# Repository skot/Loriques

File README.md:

Loriques is a solar powered Meshtastic LoRa gateway. *Warning: Loriques is very much a work in progress.*

- Designed to work with a small 6V solar panel. Like the [Voltaic 6 Watt Panel](https://voltaicsystems.com/6-watt-panel/)
- [EBYTE E22-900M30S](https://www.cdebyte.com/products/E22-900M30S/3) 30dBm LoRa tranciever
  - Untested; I picked this because it's in the Meshtastic supported LoRa ISM band, and it has one of the highest listed output power of LoRa modules.
  - Selecting a good high-gain antenna for this module is TBD.
- ESP32S3 WiFi and BLE SoC
- OLED Display
- Holders for three 18650 Lithium Ion batteries
- MCP73871 Solar charge controller
  - Optimized for solar charging and load sharing, but not a "true MPPT" controller. More info from [Adafruit](https://learn.adafruit.com/usb-dc-and-solar-lipoly-charger/design-notes)
- MAX17263 Battery fuel Guage
- HDC3020 Temperature and humidity sensor
  - This is helpful for monitoring how waterproof your outdoor enclosure is. 
- Very low noise, filtered 3.3V voltage regulator
- PCB designed to fit into the [Polycase ML-46F](https://www.polycase.com/ml-46f#ML-46F*15) Outdoor NEMA Enclosure
- ESP32 Firmware is **not** started yet!
  - There are some big challenges here, like getting the ESP32S3 and it's radios in, and out of a low power state.

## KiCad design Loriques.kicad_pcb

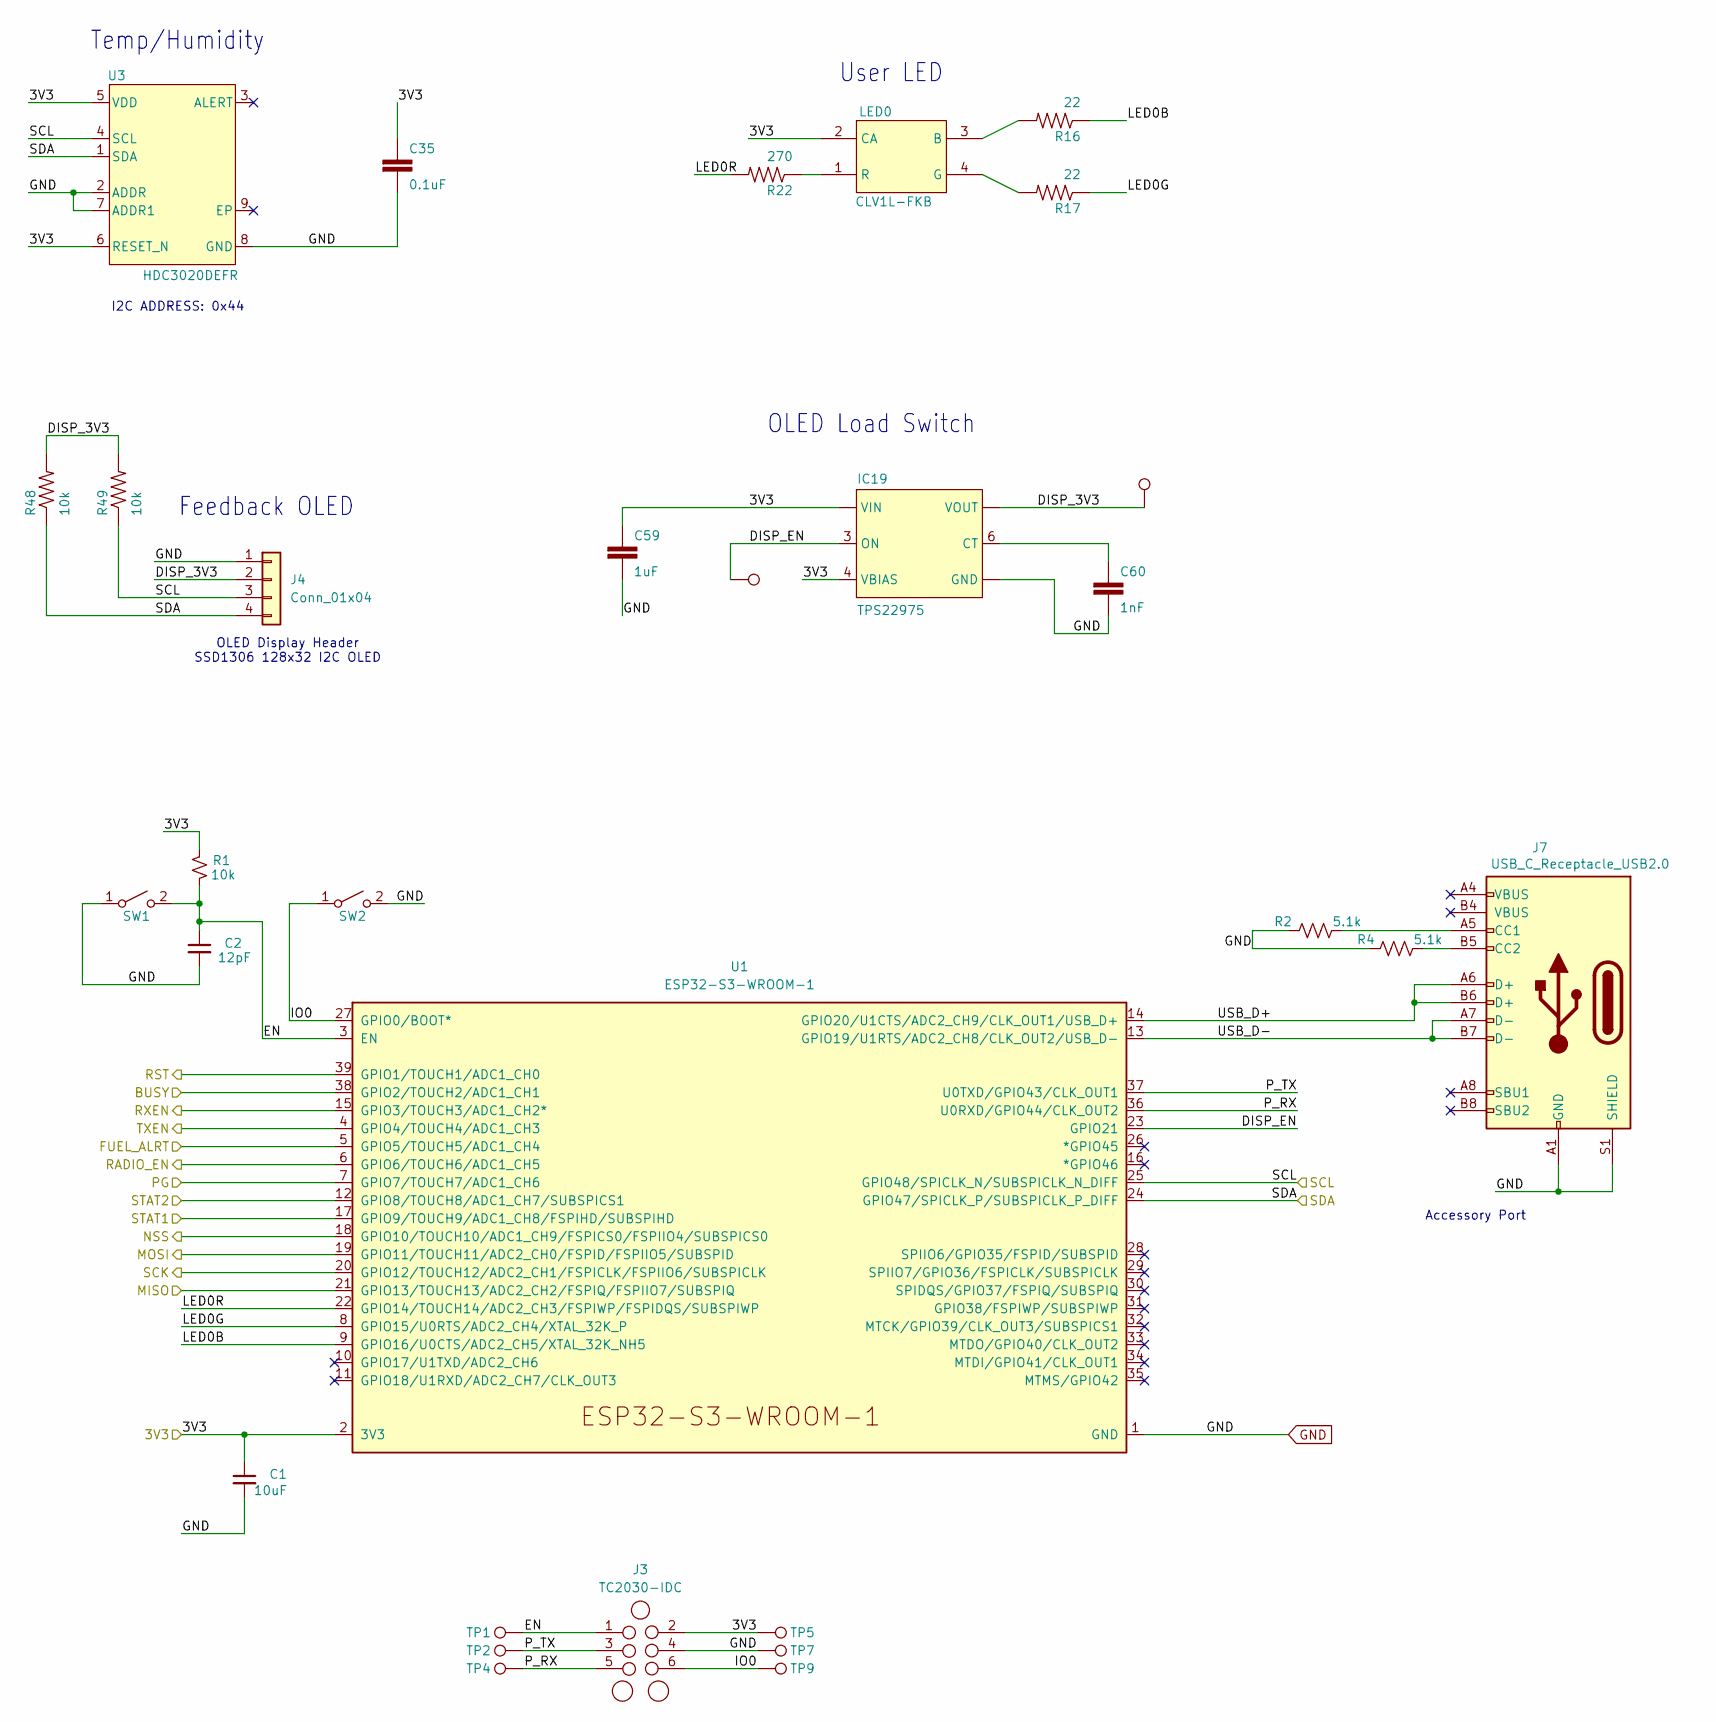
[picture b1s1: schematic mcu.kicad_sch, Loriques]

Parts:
C1: 10uF; C_0603_1608Metric; Voltage 25V; PARTNO GRM188R61E106KA73D
C2: 12pF; C_0402_1005Metric; Voltage 50V; PARTNO CC0402JRNPO9BN120
C35: 0.1uF; C_0402_1005Metric; PARTNO CL05B104KO5NNNC
C59: 1uF; C_0402_1005Metric; PARTNO GRT155R61E105KE01D
C60: 1nF; C_0402_1005Metric; PARTNO CC0402KRX7R8BB102
IC19: TPS22975; WSON8; PARTNO TPS22975DSGR
J3: TC2030-IDC; Tag-Connect_TC2030-IDC-NL_2x03_P1.27mm_Vertical
J4: Conn_01x04; PinHeader_1x04_P2.54mm_Vertical_shifted
J7: USB_C_Receptacle_USB2.0; CONN_12402032E202A_AMP; PARTNO 12402032E202A
LED0: CLV1L-FKB; PLCC140P350X320X210-4; PARTNO CLV1A-FKB-CK1VW1DE1BB7C3C3
R1: 10k; R_0402_1005Metric; PARTNO RC0402JR-0710KL
R2, R4: 5.1k; R_0402_1005Metric; PARTNO RMCF0402JT5K10; LCSC C25905
R16, R17: 22; R_0402_1005Metric; PARTNO CRGCQ0402J22R
R22: 270; R_0402_1005Metric; PARTNO CRGCQ0402F270R
R48, R49: 10k; R_0402_1005Metric
SW1: SWITCH-SPST; SW_CS1213AGF260_CRS; PARTNO CS1213AGF260; LCSC C5578986
SW2: SWITCH-SPST; SW_CS1213AGF260_CRS; PARTNO CS1213AGF260
S_3V1: TEST-POINT3X5; TestPoint_Pad_D1.5mm
TP1, TP2, TP4, TP5, TP7, TP9: TestPoint; TestPoint_Pad_D1.5mm
TP3: TEST-POINT3X5; TestPoint_Pad_D1.5mm
U1: ESP32-S3-WROOM-1; PARTNO ESP32-S3-WROOM-1-N16R8
U3: HDC3020DEFR; DEF0008A-IPC_A; PARTNO HDC3020DEFR

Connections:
/FUEL: U1.5 (GPIO5/TOUCH5/ADC1_CH4); also elsewhere on the board
/MCU/3V3: C1.1, C35.1, C59.1, IC19.1 (VIN), IC19.2 (VIN), IC19.4 (VBIAS), J3.2, LED0.2 (CA), R1.2, TP5.1, U1.2 (3V3), U3.5 (VDD), U3.6 (RESET_N); also elsewhere on the board
/MCU/DISP_3V3: IC19.7 (VOUT), IC19.8 (VOUT), J4.2, R48.2, R49.2, S_3V1.1
/MCU/DISP_EN: IC19.3 (ON), TP3.1, U1.23 (GPIO21)
/MCU/EN: C2.1, J3.1, R1.1, SW1.2 (B), TP1.1, U1.3 (EN)
/MCU/IO0: J3.6, SW2.1 (A), TP9.1, U1.27 (GPIO0/BOOT*)
/MCU/LED0B: R16.1, U1.9 (GPIO16/U0CTS/ADC2_CH5/XTAL_32K_NH5)
/MCU/LED0G: R17.1, U1.8 (GPIO15/U0RTS/ADC2_CH4/XTAL_32K_P)
/MCU/LED0R: R22.2, U1.22 (GPIO14/TOUCH14/ADC2_CH3/FSPIWP/FSPIDQS/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)
/MCU/PG: U1.7 (GPIO7/TOUCH7/ADC1_CH6); also elsewhere on the board
/MCU/P_RX: J3.5, TP4.1, U1.36 (U0RXD/GPIO44/CLK_OUT2)
/MCU/P_TX: J3.3, TP2.1, U1.37 (U0TXD/GPIO43/CLK_OUT1)
/MCU/RADIO_EN: U1.6 (GPIO6/TOUCH6/ADC1_CH5); also elsewhere on the board
/MCU/STAT1: U1.17 (GPIO9/TOUCH9/ADC1_CH8/FSPIHD/SUBSPIHD); also elsewhere on the board
/MCU/STAT2: U1.12 (GPIO8/TOUCH8/ADC1_CH7/SUBSPICS1); also elsewhere on the board
/MCU/USB_D+: J7.A6 (D+), J7.B6 (D+), U1.14 (GPIO20/U1CTS/ADC2_CH9/CLK_OUT1/USB_D+)
/MCU/USB_D-: J7.A7 (D-), J7.B7 (D-), U1.13 (GPIO19/U1RTS/ADC2_CH8/CLK_OUT2/USB_D-)
/Radio/BUSY_MCU: U1.38 (GPIO2/TOUCH2/ADC1_CH1); also elsewhere on the board
/Radio/MISO_MCU: U1.21 (GPIO13/TOUCH13/ADC2_CH2/FSPIQ/FSPIIO7/S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); also elsewhere on the board
/Radio/MOSI_MCU: U1.19 (GPIO11/TOUCH11/ADC2_CH0/FSPID/FSPIIO5/S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); also elsewhere on the board
/Radio/NSS_MCU: U1.18 (GPIO10/TOUCH10/ADC1_CH9/FSPICS0/FSPIIO4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); also elsewhere on the board
/Radio/RST_MCU: U1.39 (GPIO1/TOUCH1/ADC1_CH0); also elsewhere on the board
/Radio/RXEN_MCU: U1.15 (GPIO3/TOUCH3/ADC1_CH2*); also elsewhere on the board
/Radio/SCK_MCU: U1.20 (GPIO12/TOUCH12/ADC2_CH1/FSPICLK/FSPIIO6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); also elsewhere on the board
/Radio/TXEN_MCU: U1.4 (GPIO4/TOUCH4/ADC1_CH3); also elsewhere on the board
/SCL: J4.3, R49.1, U1.25 (GPIO48/SPICLK_N/SUBSPICLK_N_DIFF), U3.4 (SCL); also elsewhere on the board
/SDA: J4.4, R48.1, U1.24 (GPIO47/SPICLK_P/SUBSPICLK_P_DIFF), U3.1 (SDA); also elsewhere on the board
GND: C1.2, C2.2, C35.2, C59.2, C60.2, IC19.5 (GND), IC19.PP (GND), J3.4, J4.1, J7.A1 (GND), J7.B1 (GND), J7.S1 (SHIELD), R2.1, R4.1, SW1.1 (A), SW2.2 (B), TP7.1, U1.1 (GND), U1.40 (GND), U1.41 (GND), U3.2 (ADDR), U3.7 (ADDR1), U3.8 (GND); also elsewhere on the board
unnamed: C60.1, IC19.6 (CT)
unnamed: J7.A5 (CC1), R2.2
unnamed: J7.B5 (CC2), R4.2
unnamed: LED0.3 (B), R16.2
unnamed: LED0.4 (G), R17.2
unnamed: LED0.1 (R), R22.1

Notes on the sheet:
Temp/Humidity
Accessory Port
Feedback OLED
OLED Load Switch
OLED Display Header SSD1306 128x32 I2C OLED
User LED
I2C ADDRESS: 0x44

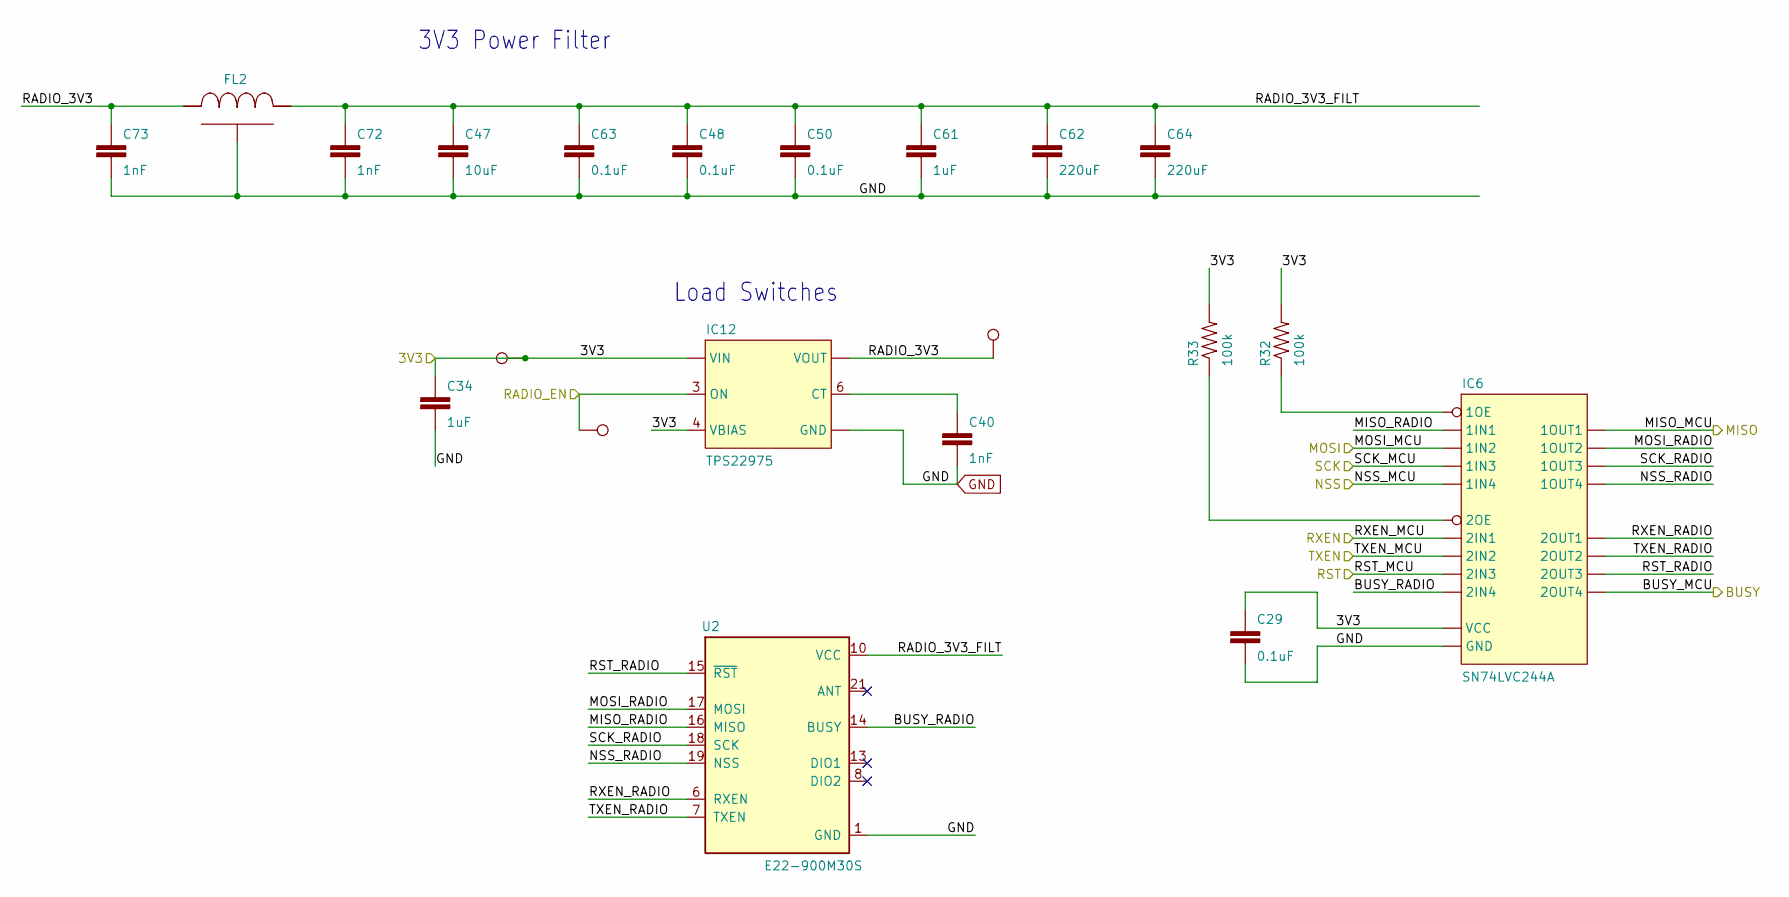
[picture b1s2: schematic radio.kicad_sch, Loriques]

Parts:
C29, C48, C50, C63: 0.1uF; C_0402_1005Metric; PARTNO CL05A104KA5NNNC
C34, C61: 1uF; C_0402_1005Metric; PARTNO GRT155R61E105KE01D
C40, C72, C73: 1nF; C_0402_1005Metric; PARTNO CC0402KRX7R8BB102
C47: 10uF; C_1206_3216Metric; PARTNO CL31B106KOHNNWE
C62, C64: 220uF; C_1210_3225Metric; PARTNO GRM32ER60J227ME05L
FL2: YFF31HC2A104MT000N; PARTNO YFF31HC2A105MT000N
IC6: SN74LVC244A; R-PVQFN-N20
IC12: TPS22975; WSON8; PARTNO TPS22975DSGR
R32, R33: 100k; R_0402_1005Metric; PARTNO RC0402FR-07100KL
S_3V3: TEST-POINT3X5; TestPoint_Pad_D1.5mm
TP6, TP8: TEST-POINT3X5; TestPoint_Pad_D1.5mm
U2: E22-900M30S

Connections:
/MCU/3V3: C29.1, C34.1, IC6.20 (VCC), IC12.1 (VIN), IC12.2 (VIN), IC12.4 (VBIAS), R32.2, R33.2, TP6.1; also elsewhere on the board
/MCU/RADIO_EN: IC12.3 (ON), TP8.1; also elsewhere on the board
/Radio/BUSY_MCU: IC6.3 (2OUT4); also elsewhere on the board
/Radio/BUSY_RADIO: IC6.17 (2IN4), U2.14 (BUSY)
/Radio/MISO_MCU: IC6.18 (1OUT1); also elsewhere on the board
/Radio/MISO_RADIO: IC6.2 (1IN1), U2.16 (MISO)
/Radio/MOSI_MCU: IC6.4 (1IN2); also elsewhere on the board
/Radio/MOSI_RADIO: IC6.16 (1OUT2), U2.17 (MOSI)
/Radio/NSS_MCU: IC6.8 (1IN4); also elsewhere on the board
/Radio/NSS_RADIO: IC6.12 (1OUT4), U2.19 (NSS)
/Radio/RADIO_3V3: C73.1, FL2.1, IC12.7 (VOUT), IC12.8 (VOUT), S_3V3.1
/Radio/RST_MCU: IC6.15 (2IN3); also elsewhere on the board
/Radio/RST_RADIO: IC6.5 (2OUT3), U2.15 (~RST)
/Radio/RXEN_MCU: IC6.11 (2IN1); also elsewhere on the board
/Radio/RXEN_RADIO: IC6.9 (2OUT1), U2.6 (RXEN)
/Radio/SCK_MCU: IC6.6 (1IN3); also elsewhere on the board
/Radio/SCK_RADIO: IC6.14 (1OUT3), U2.18 (SCK)
/Radio/TXEN_MCU: IC6.13 (2IN2); also elsewhere on the board
/Radio/TXEN_RADIO: IC6.7 (2OUT2), U2.7 (TXEN)
GND: C29.2, C34.2, C40.2, C47.2, C48.2, C50.2, C61.2, C62.2, C63.2, C64.2, C72.2, C73.2, FL2.GND, IC6.10 (GND), IC6.21 (GND), IC12.5 (GND), IC12.PP (GND), U2.1 (GND), U2.2 (GND), U2.3 (GND), U2.4 (GND), U2.5 (GND), U2.11 (GND), U2.12 (GND), U2.20 (GND), U2.22 (GND); also elsewhere on the board
unnamed: IC6.1 (1OE), R32.1
unnamed: IC6.19 (2OE), R33.1
unnamed: C40.1, IC12.6 (CT)
VCC: C47.1, C48.1, C50.1, C61.1, C62.1, C63.1, C64.1, C72.1, FL2.3 (2), U2.9 (VCC), U2.10 (VCC)

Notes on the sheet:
3V3 Power Filter
Load Switches

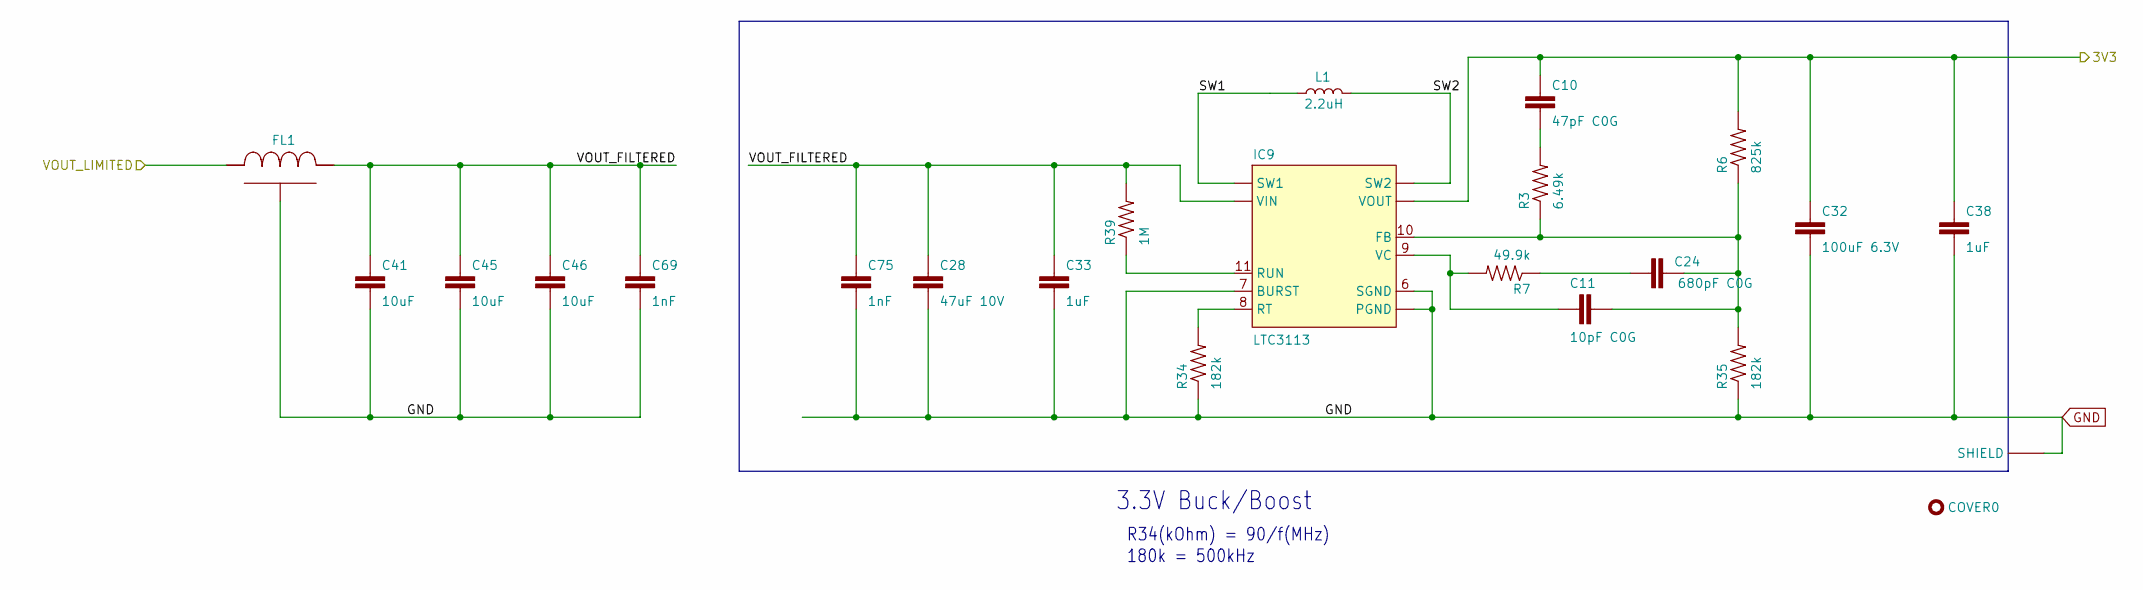
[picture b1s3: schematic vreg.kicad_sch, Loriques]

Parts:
C10: 47pF C0G; C_0402_1005Metric; PARTNO C1005C0G1H470J050BA
C11: 10pF C0G; C_0402_1005Metric; PARTNO CL05C100DB5NNNC
C24: 680pF C0G; C_0402_1005Metric; PARTNO CL05C681JB5NNNC
C28: 47uF 10V; C_1812_4532Metric; PARTNO C4532X5R1A476M280KA
C32: 100uF 6.3V; C_1812_4532Metric; PARTNO C4532X5R0J107M280KA
C33, C38: 1uF; C_0603_1608Metric; PARTNO CL10A105KA8NNNC
C41, C45, C46: 10uF; C_1206_3216Metric; PARTNO CL31B106KOHNNWE
C69, C75: 1nF; C_0402_1005Metric; PARTNO CC0402KRX7R8BB102
COVER0: BULLET; NOTHING; PARTNO MS288-10C
FL1: YFF31HC2A104MT000N; PARTNO YFF31HC2A105MT000N
IC9: LTC3113; SON50P400X500X80-17T244X434N; PARTNO LTC3113IDHD#TRPBF
L1: 2.2uH; IND_IHLP-2525CZ_VIS; PARTNO IHLP2525CZER2R2MA1
R3: 6.49k; R_0402_1005Metric; PARTNO RMCF0402FT6K49
R6: 825k; R_0402_1005Metric; PARTNO RC0402FR-07825KL
R7: 49.9k; R_0402_1005Metric; PARTNO RC0402FR-0749K9L
R34: 182k; R_0402_1005Metric; PARTNO ERJ-2RKF1823X
R35: 182k; R_0402_1005Metric; PARTNO RMCF0402FT182K
R39: 1M; R_0402_1005Metric; PARTNO CRCW04021M00FKEDC
S1: MS288-10F

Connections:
/MCU/3V3: C10.1, C32.1, C38.1, IC9.1 (VOUT), IC9.2 (VOUT), R6.2; also elsewhere on the board
/Power Input/VOUT_LIMITED: FL1.1; also elsewhere on the board
/Voltage Regulator/SW1: IC9.12 (SW1), IC9.13 (SW1), IC9.14 (SW1), L1.1
/Voltage Regulator/SW2: IC9.15 (SW2), IC9.16 (SW2), L1.2
/Voltage Regulator/VOUT_FILTERED: C28.1, C33.1, C41.1, C45.1, C46.1, C69.1, C75.1, FL1.3 (2), IC9.3 (VIN), IC9.4 (VIN), IC9.5 (VIN), R39.2
GND: C28.2, C32.2, C33.2, C38.2, C41.2, C45.2, C46.2, C69.2, C75.2, FL1.GND, IC9.6 (SGND), IC9.7 (BURST), IC9.17 (PGND), R34.1, R35.1, S1.1 (SHIELD); also elsewhere on the board
unnamed: C10.2, R3.2
unnamed: C24.1, R7.1
unnamed: C11.2, C24.2, IC9.10 (FB), R3.1, R6.1, R35.2
unnamed: IC9.8 (RT), R34.2
unnamed: IC9.11 (RUN), R39.1
unnamed: C11.1, IC9.9 (VC), R7.2

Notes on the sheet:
180k = 500kHz
R34(kOhm) = 90/f(MHz)
3.3V Buck/Boost

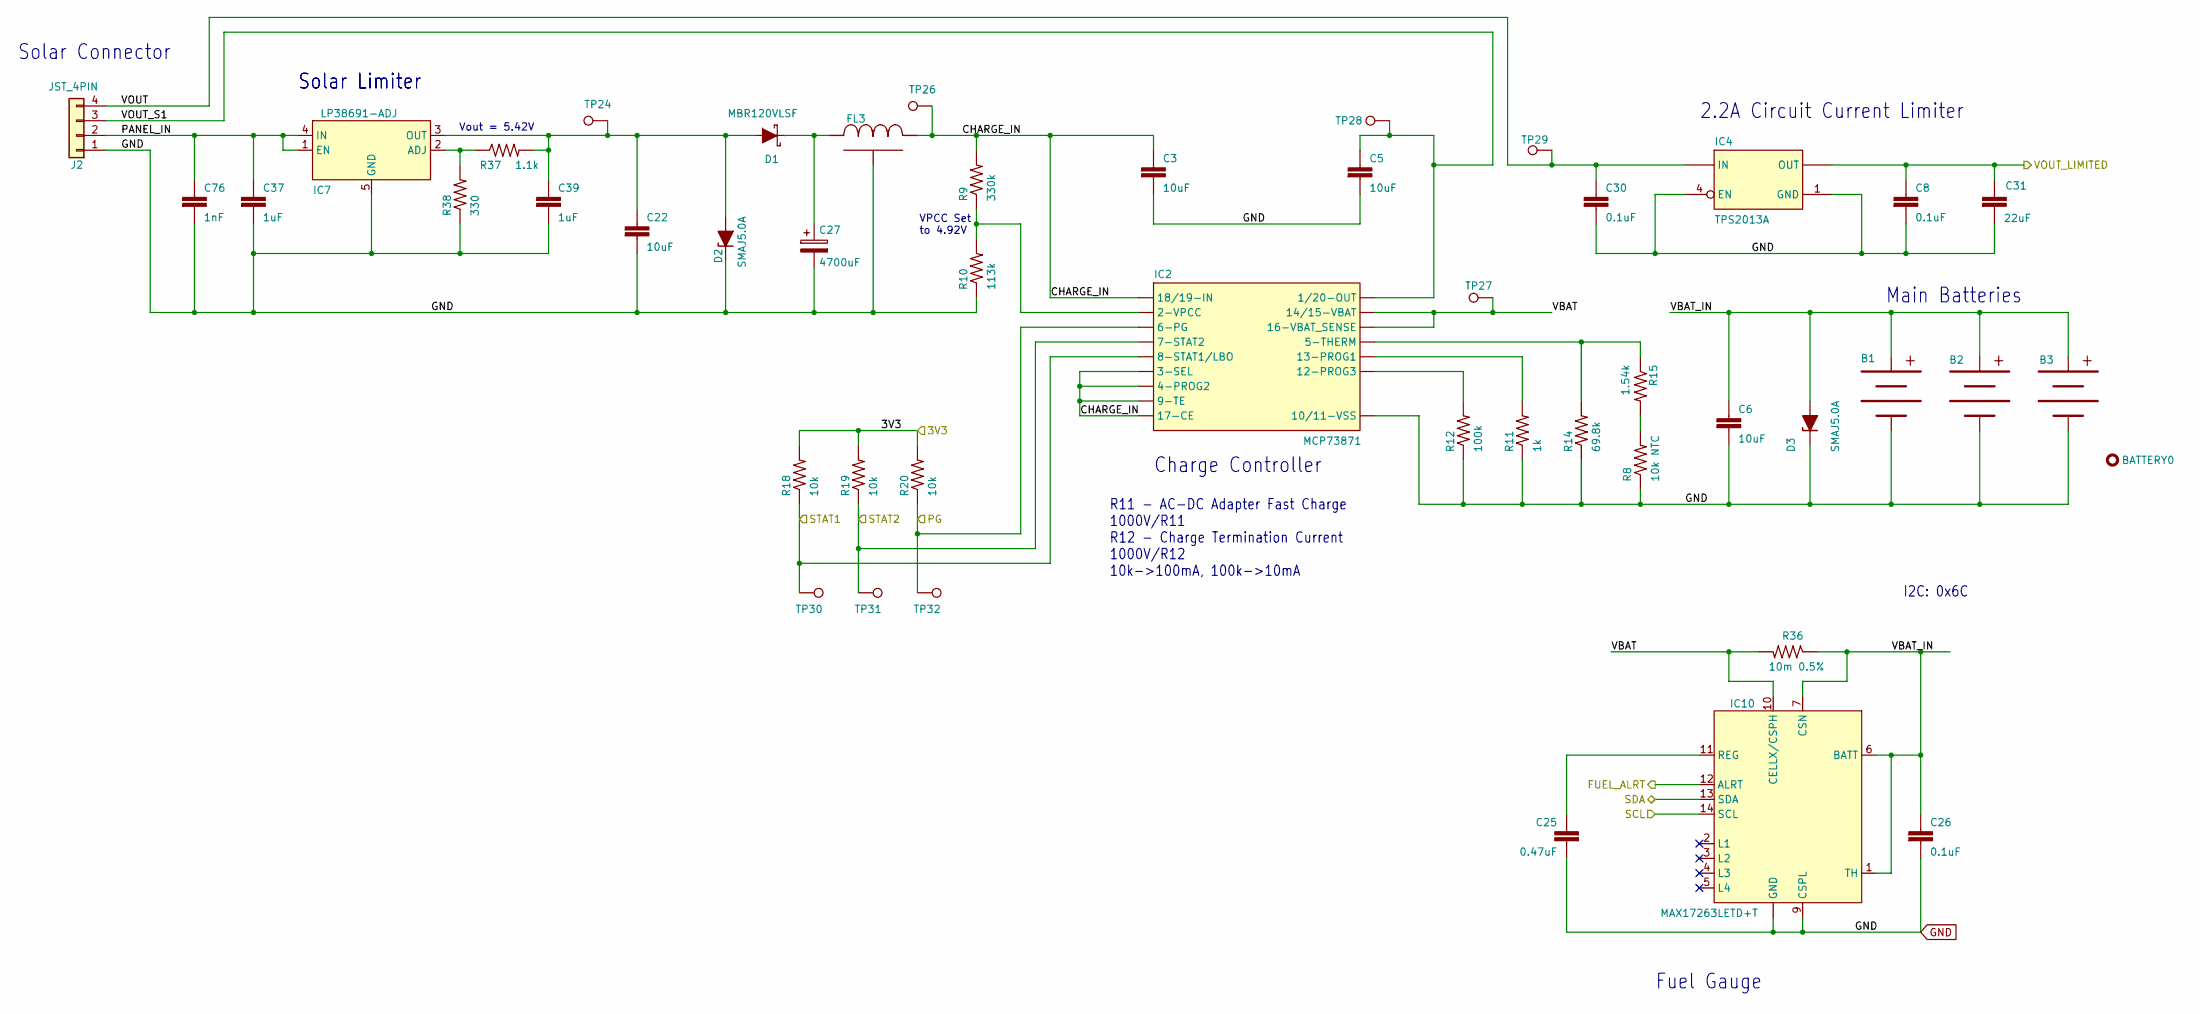
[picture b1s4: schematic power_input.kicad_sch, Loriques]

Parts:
B1, B2, B3: 18650_1042; 1042
BATTERY0: BULLET; NOTHING
C3, C5, C6, C22: 10uF; C_0603_1608Metric; PARTNO GRM188R6YA106MA73D
C8, C26, C30: 0.1uF; C_0402_1005Metric; PARTNO CL05A104KA5NNNC
C25: 0.47uF; C_0402_1005Metric; PARTNO GRT155R61E474ME01D
C27: 4700uF; CP_Radial_D16.0mm_P7.50mm; PARTNO 25PK4700MEFC16X25
C31: 22uF; C_0805_2012Metric; PARTNO GRM21BR61E226ME44L
C37, C39: 1uF; C_0402_1005Metric; PARTNO C1005X5R1V105K050BE
C76: 1nF; C_0402_1005Metric; PARTNO CC0402KRX7R8BB102
D1: MBR120VLSF; SOD−123FL; PARTNO MBR120VLSFT1G
D2, D3: SMAJ5.0A; D_SMA; PARTNO SMAJ5.0A
FL3: YFF31HC2A104MT000N; PARTNO YFF31HC2A105MT000N
IC2: MCP73871; QFN20-ML_4X4MM; PARTNO MCP73871-2CCI/ML
IC4: TPS2013A; R-PDSO-G8_NOPAD; PARTNO TPS2013AD
IC7: LP38691-ADJ; SOT-223-5; PARTNO LP38693MP-ADJ/NOPB
IC10: MAX17263LETD+T; SON40P300X300X80-15T170X230N; PARTNO MAX17263LETD+T
J2: JST_4PIN; JST-PH-4-SMT; PARTNO B4B-PH-SM4-TB
R8: 10k NTC; R_0402_1005Metric; PARTNO ERT-J0EM103J
R9: 330k; R_0402_1005Metric; PARTNO RC0402JR-07330KL
R10: 113k; R_0402_1005Metric; PARTNO RC0402FR-07113KL
R11: 1k; R_0402_1005Metric; PARTNO RC0402FR-071KL
R12: 100k; R_0402_1005Metric; PARTNO RC0402FR-07100KL
R14: 69.8k; R_0402_1005Metric; PARTNO RC0402FR-0769K8L
R15: 1.54k; R_0402_1005Metric; PARTNO RC0402FR-071K54L
R18, R19, R20: 10k; R_0402_1005Metric; PARTNO RC0402FR-0710KL
R36: 10m 0.5%; R_1206_3216Metric; PARTNO PCS1206DR0100ET
R37: 1.1k; R_0402_1005Metric; PARTNO RC0402FR-071K1L
R38: 330; R_0402_1005Metric; PARTNO RC0402FR-07330RL
TP24, TP26, TP27, TP28, TP29, TP30, TP31, TP32: TEST-POINT3X5; TestPoint_Pad_D1.5mm

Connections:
/FUEL: IC10.12 (ALRT); also elsewhere on the board
/MCU/3V3: R18.2, R19.2, R20.2; also elsewhere on the board
/MCU/PG: IC2.6 (6-PG), R20.1, TP32.1; also elsewhere on the board
/MCU/STAT1: IC2.8 (8-STAT1/LBO), R18.1, TP30.1; also elsewhere on the board
/MCU/STAT2: IC2.7 (7-STAT2), R19.1, TP31.1; also elsewhere on the board
/Power Input/CHARGE_IN: C3.1, FL3.3 (2), IC2.3 (3-SEL), IC2.4 (4-PROG2), IC2.9 (9-TE), IC2.17 (17-CE), IC2.18 (18/19-IN), IC2.19 (18/19-IN), R9.2, TP26.1
/Power Input/PANEL_IN: C37.1, C76.1, IC7.1 (EN), IC7.4 (IN), J2.2
/Power Input/VBAT: IC2.14 (14/15-VBAT), IC2.15 (14/15-VBAT), IC2.16 (16-VBAT_SENSE), IC10.10 (CELLX/CSPH), R36.2, TP27.1
/Power Input/VBAT_IN: B1.+, B2.+, B3.+, C6.1, C26.1, D3.2 (A), IC10.1 (TH), IC10.6 (BATT), IC10.7 (CSN), R36.1
/Power Input/VOUT: C30.1, IC4.2 (IN), IC4.3 (IN), J2.4, TP29.1
/Power Input/VOUT_LIMITED: C8.1, C31.1, IC4.5 (OUT), IC4.6 (OUT), IC4.7 (OUT), IC4.8 (OUT); also elsewhere on the board
/Power Input/VOUT_S1: C5.1, IC2.1 (1/20-OUT), IC2.20 (1/20-OUT), J2.3, TP28.1
/SCL: IC10.14 (SCL); also elsewhere on the board
/SDA: IC10.13 (SDA); also elsewhere on the board
GND: B1.-, B2.-, B3.-, C3.2, C5.2, C6.2, C8.2, C22.2, C25.2, C26.2, C27.2, C30.2, C31.2, C37.2, C39.2, C76.2, D2.1 (K), D3.1 (K), FL3.GND, IC2.10 (10/11-VSS), IC2.11 (10/11-VSS), IC2.EP (10/11-VSS), IC4.1 (GND), IC4.4 (EN), IC7.5 (GND), IC10.8 (GND), IC10.9 (CSPL), IC10.15 (GND), J2.1, R8.1, R10.1, R11.1, R12.1, R14.1, R38.1; also elsewhere on the board
unnamed: C27.1, D1.K, FL3.1
unnamed: C22.1, C39.1, D1.A, D2.2 (A), IC7.3 (OUT), R37.2, TP24.1
unnamed: IC2.2 (2-VPCC), R9.1, R10.2
unnamed: IC2.5 (5-THERM), R14.2, R15.1
unnamed: IC2.12 (12-PROG3), R12.2
unnamed: IC2.13 (13-PROG1), R11.2
unnamed: IC7.2 (ADJ), R37.1, R38.2
unnamed: C25.1, IC10.11 (REG)
unnamed: R8.2, R15.2

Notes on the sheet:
Vout = 5.42V
Solar Connector
Fuel Gauge
2.2A Circuit Current Limiter
R11 - AC-DC Adapter Fast Charge 1000V/R11 R12 - Charge Termination Current 1000V/R12 10k->100mA, 100k->10mA
I2C: 0x6C
Solar Limiter
Charge Controller
VPCC Set to 4.92V
Main Batteries

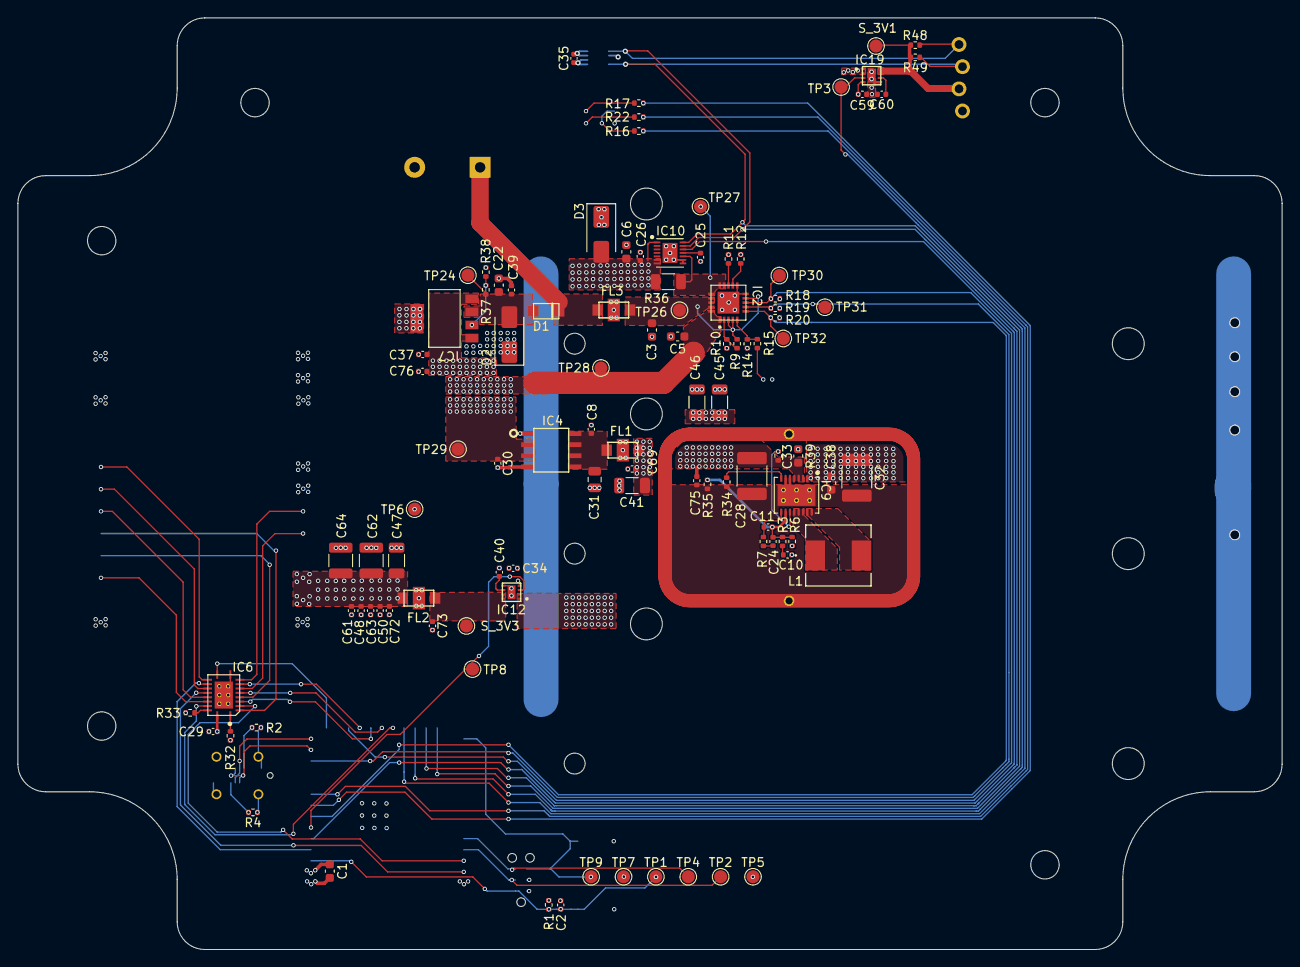
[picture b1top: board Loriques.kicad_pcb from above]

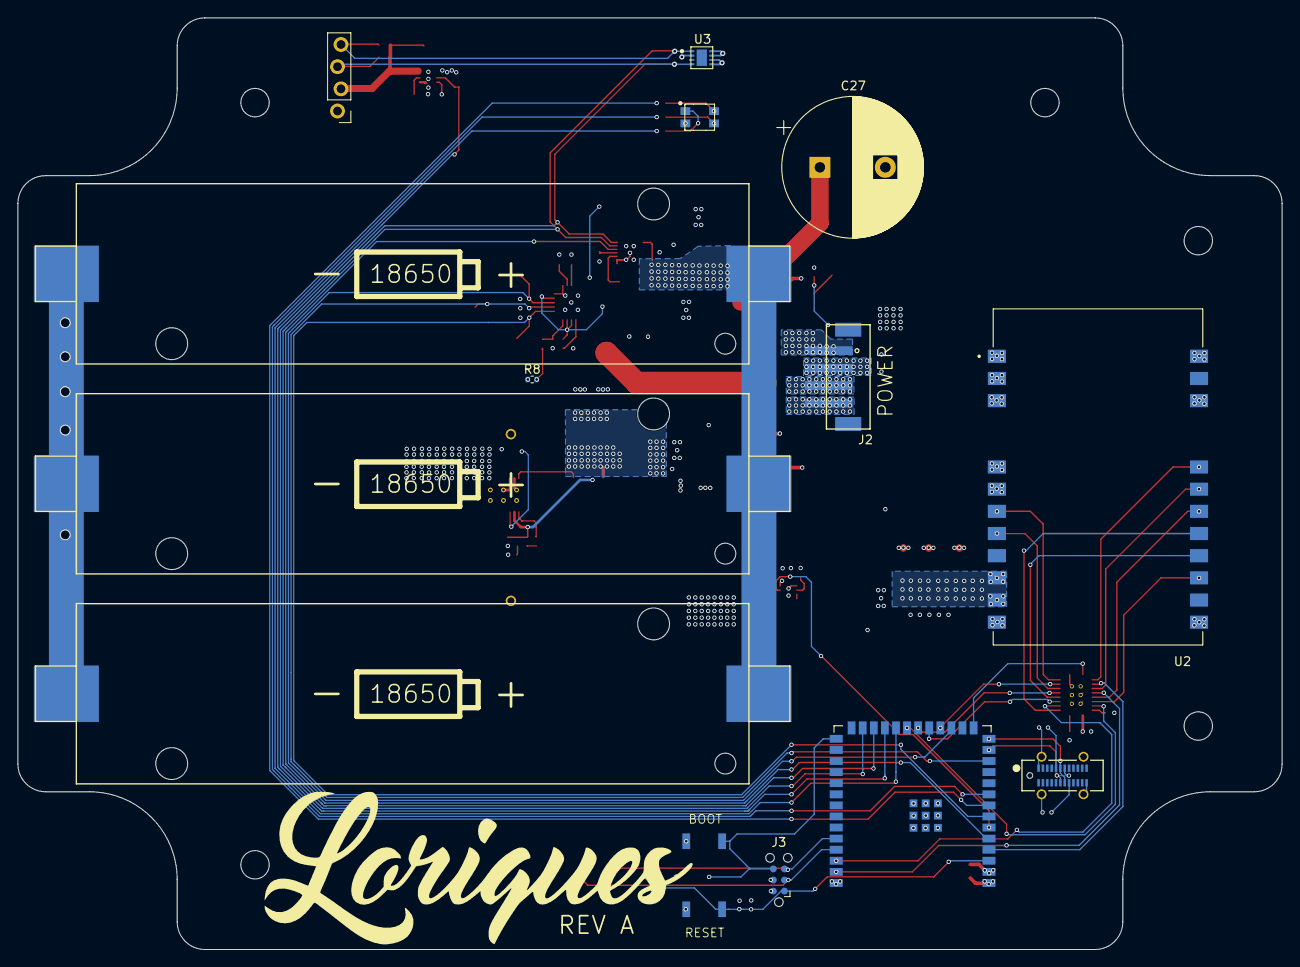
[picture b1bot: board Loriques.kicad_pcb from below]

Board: 6 copper layers, 144.8 x 106.7 mm, 121 parts (15 on the bottom side), 72 nets.

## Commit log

2025-07-11 fixed up silk screen text sizes, board outline and mounting holes
2025-07-11 name change to Loriques
2025-07-11 added logo to schematic sheets
2025-07-11 added lots of 3d models
2025-07-11 more 3D parts. changed out the temp/humidity sensor for an instock one
2025-07-11 lots of routing, tweaking placement. adding courtyards
2025-07-12 initial routing done!
2025-07-12 some DRC fixing
2025-07-12 Create LICENSE
2025-07-12 silkscreen cleanup. add readme.
2025-07-13 added solar panel info to README.md
